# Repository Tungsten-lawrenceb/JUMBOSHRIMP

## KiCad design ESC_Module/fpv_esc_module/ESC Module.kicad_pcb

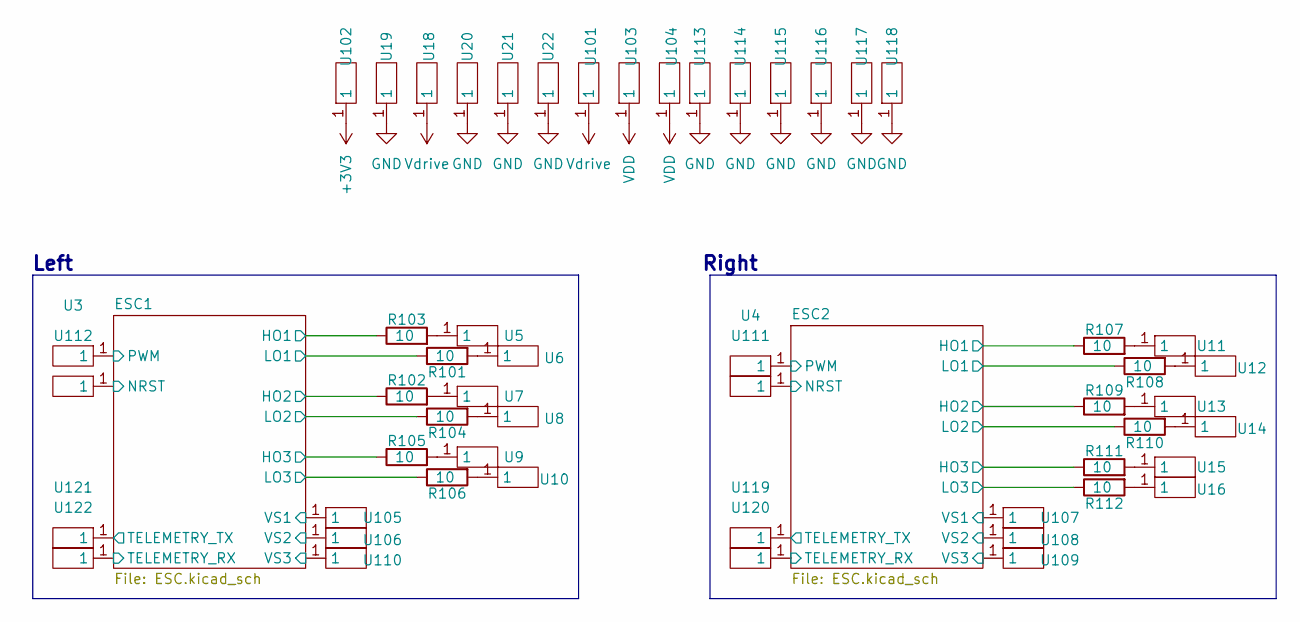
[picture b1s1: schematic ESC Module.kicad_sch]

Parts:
R101, R102, R103, R104, R105, R106, R107, R108, R109, R110, R111, R112: 10; R_0402_1005Metric
U3, U4, U5, U6, U7, U8, U9, U10, U11, U12, U13, U14, U15, U16, U18, U19, U20, U21, U22, U101, U102, U103, U104, U105, U106, U107, U108, U109, U110, U111, U112, U113, U114, U115, U116, U117, U118, U119, U120, U121, U122: Castlated_Hole

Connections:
+3V3: U102.1; also elsewhere on the board
/ESC1/HO1: R103.1; also elsewhere on the board
/ESC1/HO2: R102.1; also elsewhere on the board
/ESC1/HO3: R105.1; also elsewhere on the board
/ESC1/LO1: R101.1; also elsewhere on the board
/ESC1/LO2: R104.1; also elsewhere on the board
/ESC1/LO3: R106.1; also elsewhere on the board
/ESC1/PWM: U3.1; also elsewhere on the board
/ESC1/TELEMETRY_RX: U122.1; also elsewhere on the board
/ESC1/TELEMETRY_TX: U121.1; also elsewhere on the board
/ESC1/VS1: U105.1; also elsewhere on the board
/ESC1/VS2: U106.1; also elsewhere on the board
/ESC1/VS3: U110.1; also elsewhere on the board
/ESC2/HO1: R107.1; also elsewhere on the board
/ESC2/HO2: R109.1; also elsewhere on the board
/ESC2/HO3: R111.1; also elsewhere on the board
/ESC2/LO1: R108.1; also elsewhere on the board
/ESC2/LO2: R110.1; also elsewhere on the board
/ESC2/LO3: R112.1; also elsewhere on the board
/ESC2/PWM: U4.1; also elsewhere on the board
/ESC2/TELEMETRY_RX: U120.1; also elsewhere on the board
/ESC2/TELEMETRY_TX: U119.1; also elsewhere on the board
/ESC2/VS1: U107.1; also elsewhere on the board
/ESC2/VS2: U108.1; also elsewhere on the board
/ESC2/VS3: U109.1; also elsewhere on the board
GND: U19.1, U20.1, U21.1, U22.1, U113.1, U114.1, U115.1, U116.1, U117.1, U118.1; also elsewhere on the board
unnamed: R101.2, U6.1
unnamed: R102.2, U7.1
unnamed: R103.2, U5.1
unnamed: R104.2, U8.1
unnamed: R105.2, U9.1
unnamed: R106.2, U10.1
unnamed: R107.2, U11.1
unnamed: R108.2, U12.1
unnamed: R109.2, U13.1
unnamed: R110.2, U14.1
unnamed: R111.2, U15.1
unnamed: R112.2, U16.1
VDD: U103.1, U104.1; also elsewhere on the board
Vdrive: U18.1, U101.1; also elsewhere on the board

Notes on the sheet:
Right
Left

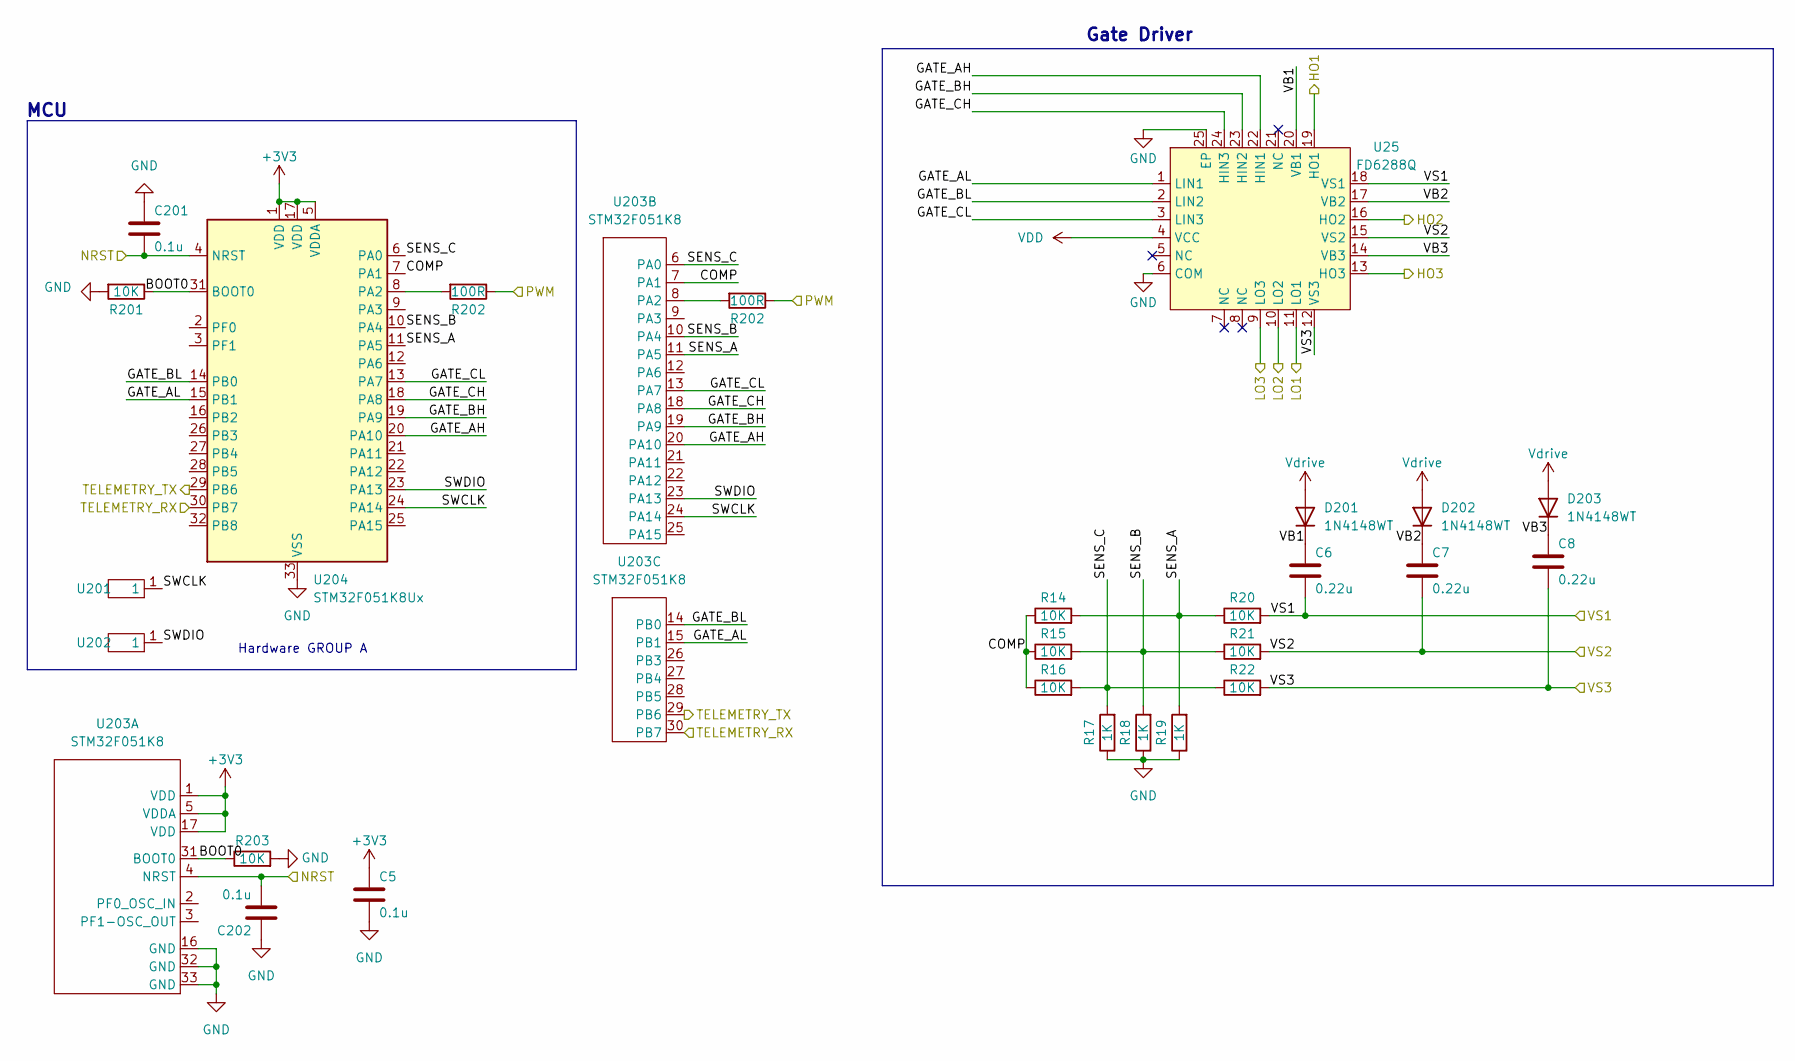
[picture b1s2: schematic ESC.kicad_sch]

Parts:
C5, C201, C202: 0.1u; C_0402_1005Metric; digikey# 490-3261-2-ND
C6, C7, C8: 0.22u; C_0603_1608Metric; digikey# 445-5191-1-ND
D201, D202, D203: 1N4148WT; D_SOD-523
R14, R15, R16, R20, R21, R22, R201, R203: 10K; R_0402_1005Metric
R17, R18, R19: 1K; R_0402_1005Metric
R202: 100R; R_0402_1005Metric
U25: FD6288Q; QFN-24-1EP_4x4mm_P0.5mm_EP2.6x2.6mm; LCSC# C328453
U201, U202: Castlated_Hole
U203: STM32F051K8; UFQFPN-32-1EP_5x5mm_P0.5mm_EP3.5x3.5mm
U204: STM32F051K8Ux; QFN-32-1EP_5x5mm_P0.5mm_EP3.45x3.45mm

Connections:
+3V3: C5.1, U204.1 (VDD), U204.5 (VDDA), U204.17 (VDD); also elsewhere on the board
/ESC1/COMP: R14.1, R15.1, R16.1, U204.7 (PA1)
/ESC1/GATE_AH: U25.22 (HIN1), U204.20 (PA10)
/ESC1/GATE_AL: U25.1 (LIN1), U204.15 (PB1)
/ESC1/GATE_BH: U25.23 (HIN2), U204.19 (PA9)
/ESC1/GATE_BL: U25.2 (LIN2), U204.14 (PB0)
/ESC1/GATE_CH: U25.24 (HIN3), U204.18 (PA8)
/ESC1/GATE_CL: U25.3 (LIN3), U204.13 (PA7)
/ESC1/HO1: U25.19 (HO1); also elsewhere on the board
/ESC1/HO2: U25.16 (HO2); also elsewhere on the board
/ESC1/HO3: U25.13 (HO3); also elsewhere on the board
/ESC1/LO1: U25.11 (LO1); also elsewhere on the board
/ESC1/LO2: U25.10 (LO2); also elsewhere on the board
/ESC1/LO3: U25.9 (LO3); also elsewhere on the board
/ESC1/PWM: R202.1; also elsewhere on the board
/ESC1/SENS_A: R14.2, R19.2, R20.1, U204.11 (PA5)
/ESC1/SENS_B: R15.2, R18.2, R21.1, U204.10 (PA4)
/ESC1/SENS_C: R16.2, R17.2, R22.1, U204.6 (PA0)
/ESC1/SWCLK: U201.1, U204.24 (PA14)
/ESC1/SWDIO: U202.1, U204.23 (PA13)
/ESC1/TELEMETRY_RX: U204.30 (PB7); also elsewhere on the board
/ESC1/TELEMETRY_TX: U204.29 (PB6); also elsewhere on the board
/ESC1/VB1: C6.1, D201.1 (K), U25.20 (VB1)
/ESC1/VB2: C7.1, D202.1 (K), U25.17 (VB2)
/ESC1/VB3: C8.1, D203.1 (K), U25.14 (VB3)
/ESC1/VS1: C6.2, R20.2, U25.18 (VS1); also elsewhere on the board
/ESC1/VS2: C7.2, R21.2, U25.15 (VS2); also elsewhere on the board
/ESC1/VS3: C8.2, R22.2, U25.12 (VS3); also elsewhere on the board
GND: C5.2, C201.1, C202.1, R17.1, R18.1, R19.1, R201.2, U25.6 (COM), U25.25 (EP), U204.33 (VSS); also elsewhere on the board
unnamed: R202.2, U204.8 (PA2)
VDD: U25.4 (VCC); also elsewhere on the board
Vdrive: D201.2 (A), D202.2 (A), D203.2 (A); also elsewhere on the board

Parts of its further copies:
C301: 0.1u; C_0402_1005Metric; digikey# 490-3261-2-ND
C302, C303, C304: 0.22u; C_0603_1608Metric; digikey# 445-5191-1-ND
D301, D302, D304: 1N4148WT; D_SOD-523
R306, R307, R308: 1K; R_0402_1005Metric
R309, R310, R311, R312: 10K; R_0402_1005Metric
R313: 100R; R_0402_1005Metric
U302: FD6288Q; QFN-24-1EP_4x4mm_P0.5mm_EP2.6x2.6mm; LCSC# C328453
U303, U304: Castlated_Hole

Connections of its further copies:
+3V3: C301.1; also elsewhere on the board
/ESC2/GATE_AH: U302.22 (HIN1); also elsewhere on the board
/ESC2/GATE_AL: U302.1 (LIN1); also elsewhere on the board
/ESC2/GATE_BH: U302.23 (HIN2); also elsewhere on the board
/ESC2/GATE_BL: U302.2 (LIN2); also elsewhere on the board
/ESC2/GATE_CH: U302.24 (HIN3); also elsewhere on the board
/ESC2/GATE_CL: U302.3 (LIN3); also elsewhere on the board
/ESC2/HO1: U302.19 (HO1); also elsewhere on the board
/ESC2/HO2: U302.16 (HO2); also elsewhere on the board
/ESC2/HO3: U302.13 (HO3); also elsewhere on the board
/ESC2/LO1: U302.11 (LO1); also elsewhere on the board
/ESC2/LO2: U302.10 (LO2); also elsewhere on the board
/ESC2/LO3: U302.9 (LO3); also elsewhere on the board
/ESC2/PWM: R313.1; also elsewhere on the board
/ESC2/SENS_A: R308.2, R309.1; also elsewhere on the board
/ESC2/SENS_B: R307.2, R310.1; also elsewhere on the board
/ESC2/SENS_C: R306.2, R311.1; also elsewhere on the board
/ESC2/SWCLK: U303.1; also elsewhere on the board
/ESC2/SWDIO: U304.1; also elsewhere on the board
/ESC2/VB1: C302.1, D304.1 (K), U302.20 (VB1)
/ESC2/VB2: C303.1, D301.1 (K), U302.17 (VB2)
/ESC2/VB3: C304.1, D302.1 (K), U302.14 (VB3)
/ESC2/VS1: C302.2, R309.2, U302.18 (VS1); also elsewhere on the board
/ESC2/VS2: C303.2, R310.2, U302.15 (VS2); also elsewhere on the board
/ESC2/VS3: C304.2, R311.2, U302.12 (VS3); also elsewhere on the board
GND: C301.2, R306.1, R307.1, R308.1, R312.2, U302.6 (COM), U302.25 (EP); also elsewhere on the board
unnamed 69: R313.2; also elsewhere on the board
VDD: U302.4 (VCC); also elsewhere on the board
Vdrive: D301.2 (A), D302.2 (A), D304.2 (A); also elsewhere on the board

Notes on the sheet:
MCU
Hardware GROUP A
Gate Driver

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
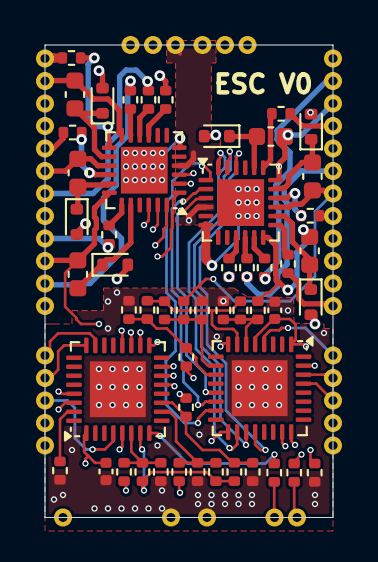
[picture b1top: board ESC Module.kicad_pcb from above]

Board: 4 copper layers, 16.0 x 26.2 mm, 97 parts (0 on the bottom side), 76 nets.

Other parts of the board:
R303, R304, R305: 1K; R_0402_1005Metric
U301: STM32F051K8Ux; QFN-32-1EP_5x5mm_P0.5mm_EP3.1x3.1mm

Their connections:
+3V3: U301.1 (VDD), U301.5 (VDDA), U301.17 (VDD); also elsewhere on the board
/ESC2/COMP: R303.1, R304.1, R305.1, U301.7 (PA1)
/ESC2/GATE_AH: U301.20 (PA10); also elsewhere on the board
/ESC2/GATE_AL: U301.15 (PB1); also elsewhere on the board
/ESC2/GATE_BH: U301.19 (PA9); also elsewhere on the board
/ESC2/GATE_BL: U301.14 (PB0); also elsewhere on the board
/ESC2/GATE_CH: U301.18 (PA8); also elsewhere on the board
/ESC2/GATE_CL: U301.13 (PA7); also elsewhere on the board
/ESC2/SENS_A: R303.2, U301.11 (PA5); also elsewhere on the board
/ESC2/SENS_B: R304.2, U301.10 (PA4); also elsewhere on the board
/ESC2/SENS_C: R305.2, U301.6 (PA0); also elsewhere on the board
/ESC2/SWCLK: U301.24 (PA14); also elsewhere on the board
/ESC2/SWDIO: U301.23 (PA13); also elsewhere on the board
/ESC2/TELEMETRY_RX: U301.30 (PB7); also elsewhere on the board
/ESC2/TELEMETRY_TX: U301.29 (PB6); also elsewhere on the board
GND: U301.16, U301.32, U301.33 (VSS); also elsewhere on the board
unnamed 69: U301.8 (PA2); also elsewhere on the board

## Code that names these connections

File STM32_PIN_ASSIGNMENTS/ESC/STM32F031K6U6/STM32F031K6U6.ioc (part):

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Mcu.Name=STM32F031K(4-6)Ux
Mcu.Package=UFQFPN32
Mcu.UserName=STM32F031K6Ux
PA0.GPIOParameters=GPIO_Label
PA0.GPIO_Label=SENS_C
PA0.Mode=IN0
PA0.Signal=ADC_IN0
PA1.GPIOParameters=GPIO_Label
PA1.GPIO_Label=COMP
PA1.Mode=IN1
PA1.Signal=ADC_IN1
PA10.GPIOParameters=GPIO_Label
PA10.GPIO_Label=GATE_AH
PA10.Signal=GPIO_Output
PA13.Mode=Serial_Wire
PA13.Signal=SYS_SWDIO
PA14.Mode=Serial_Wire
PA14.Signal=SYS_SWCLK
PA2.GPIOParameters=GPIO_Label
PA2.GPIO_Label=PWM
PA2.Signal=GPIO_Input
PA4.GPIOParameters=GPIO_Label
PA4.GPIO_Label=SENS_B
PA4.Mode=IN4
PA4.Signal=ADC_IN4
PA5.GPIOParameters=GPIO_Label
PA5.GPIO_Label=SENS_A
PA5.Mode=IN5
PA5.Signal=ADC_IN5
PA7.GPIOParameters=GPIO_Label
PA7.GPIO_Label=GATE_CL
PA7.Signal=GPIO_Output
PA8.GPIOParameters=GPIO_Label
PA8.GPIO_Label=GATE_CH
PA8.Signal=GPIO_Output
PA9.GPIOParameters=GPIO_Label
PA9.GPIO_Label=GATE_BH
PA9.Signal=GPIO_Output
PB0.GPIOParameters=GPIO_Label
PB0.GPIO_Label=GATE_BL
PB0.Signal=GPIO_Output
PB1.GPIOParameters=GPIO_Label
PB1.GPIO_Label=GATE_AL
PB1.Signal=GPIO_Output
board=custom

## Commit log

2025-11-03 First Commit
    Archive folder, STM32CubeMx files for ESC and pin assignments, comments on ESC SCH
2025-11-06 Added ESC Module
2025-11-06 FIXED Add ESC Module
    Fixed a double git thing
2025-11-06 Fixed root started working on MCU
2025-11-07 MCU Sybole made
2025-11-14 Schematic changes made
    Made changes to the schematic just starting routing
